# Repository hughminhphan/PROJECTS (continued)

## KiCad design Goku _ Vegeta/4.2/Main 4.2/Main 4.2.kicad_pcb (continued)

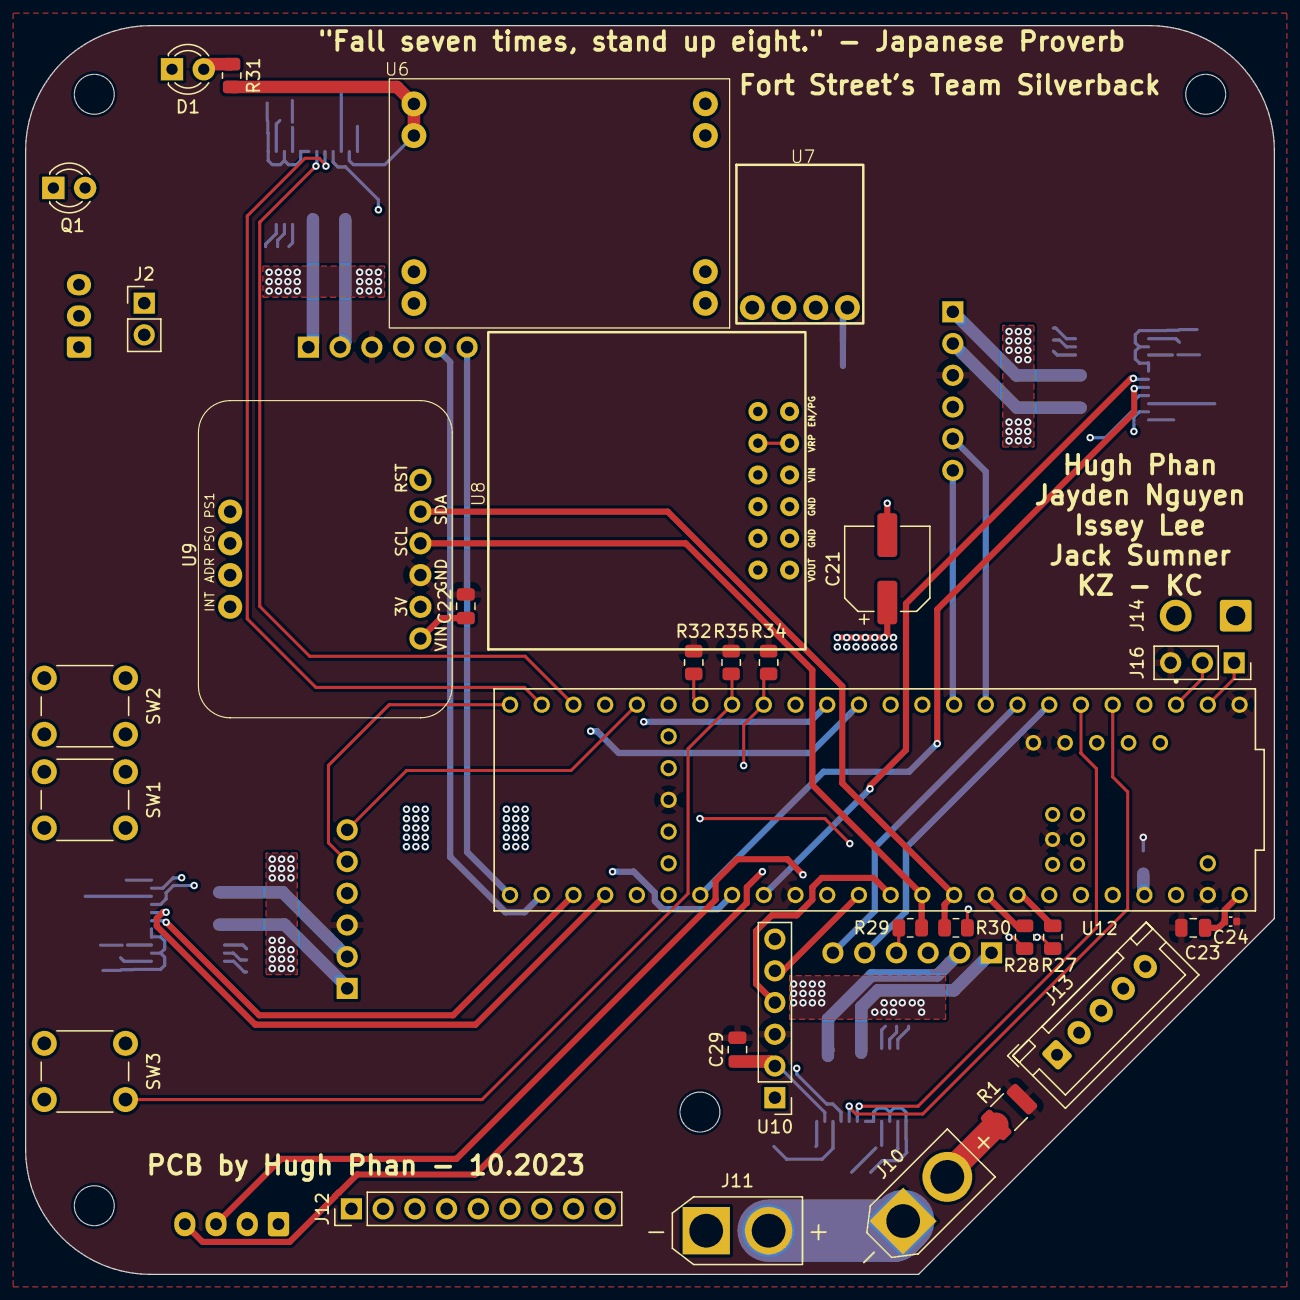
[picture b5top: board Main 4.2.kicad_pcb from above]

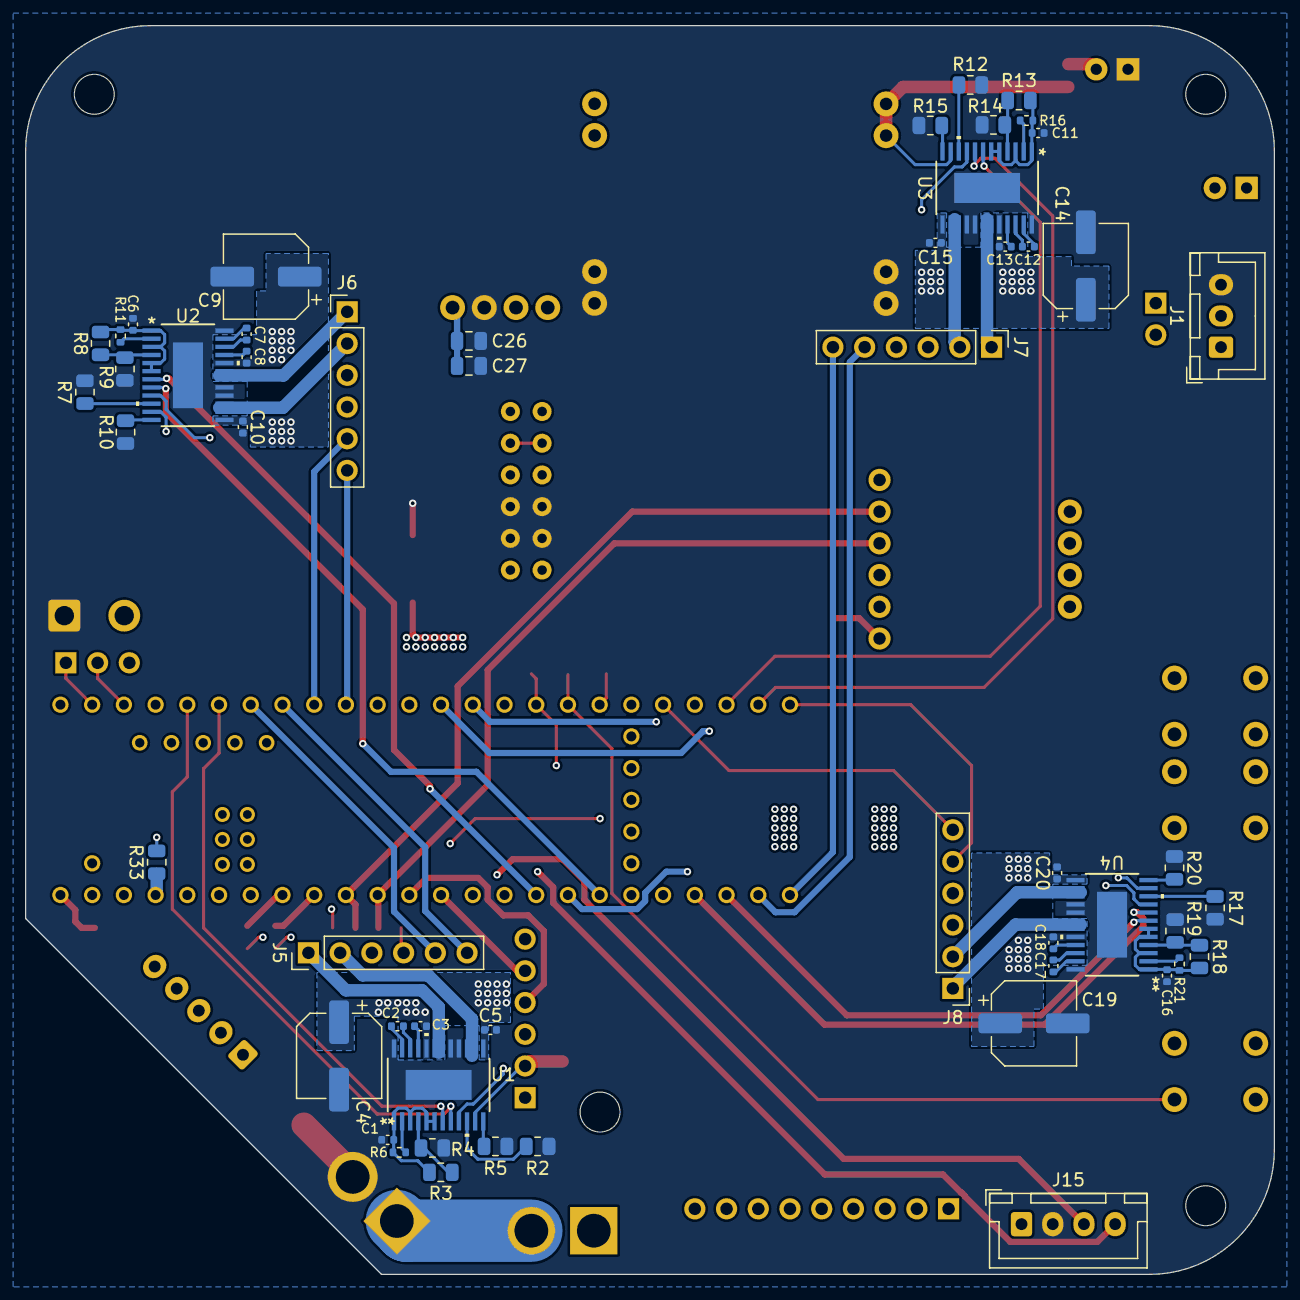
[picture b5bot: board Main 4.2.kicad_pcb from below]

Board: 4 copper layers, 100.0 x 100.0 mm, 89 parts (53 on the bottom side), 85 nets.

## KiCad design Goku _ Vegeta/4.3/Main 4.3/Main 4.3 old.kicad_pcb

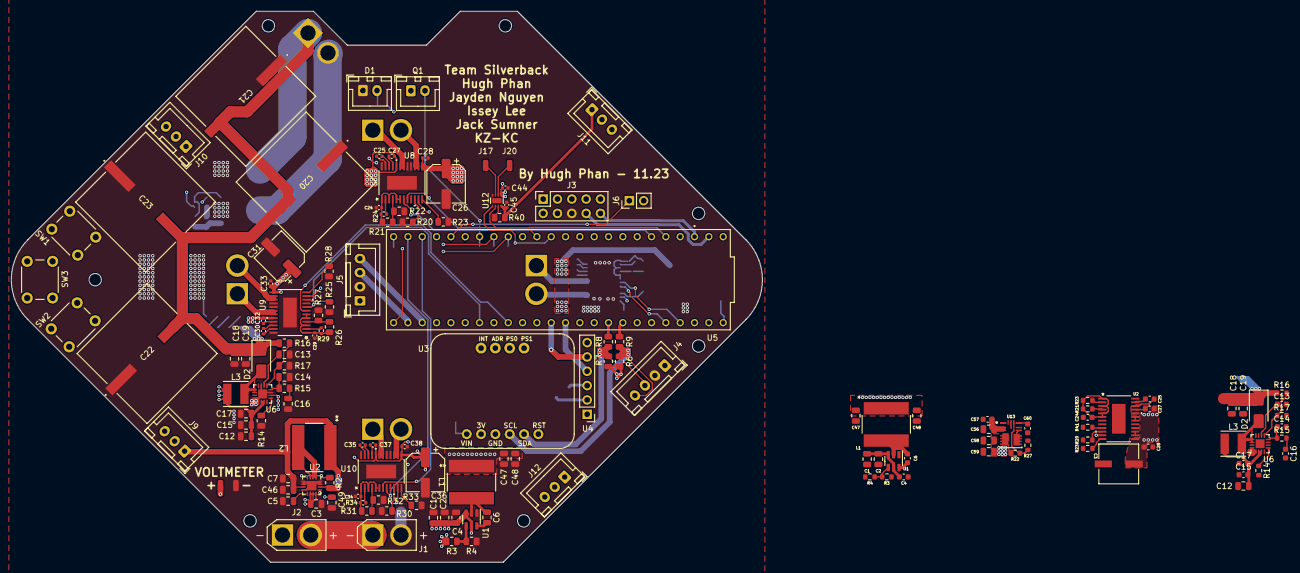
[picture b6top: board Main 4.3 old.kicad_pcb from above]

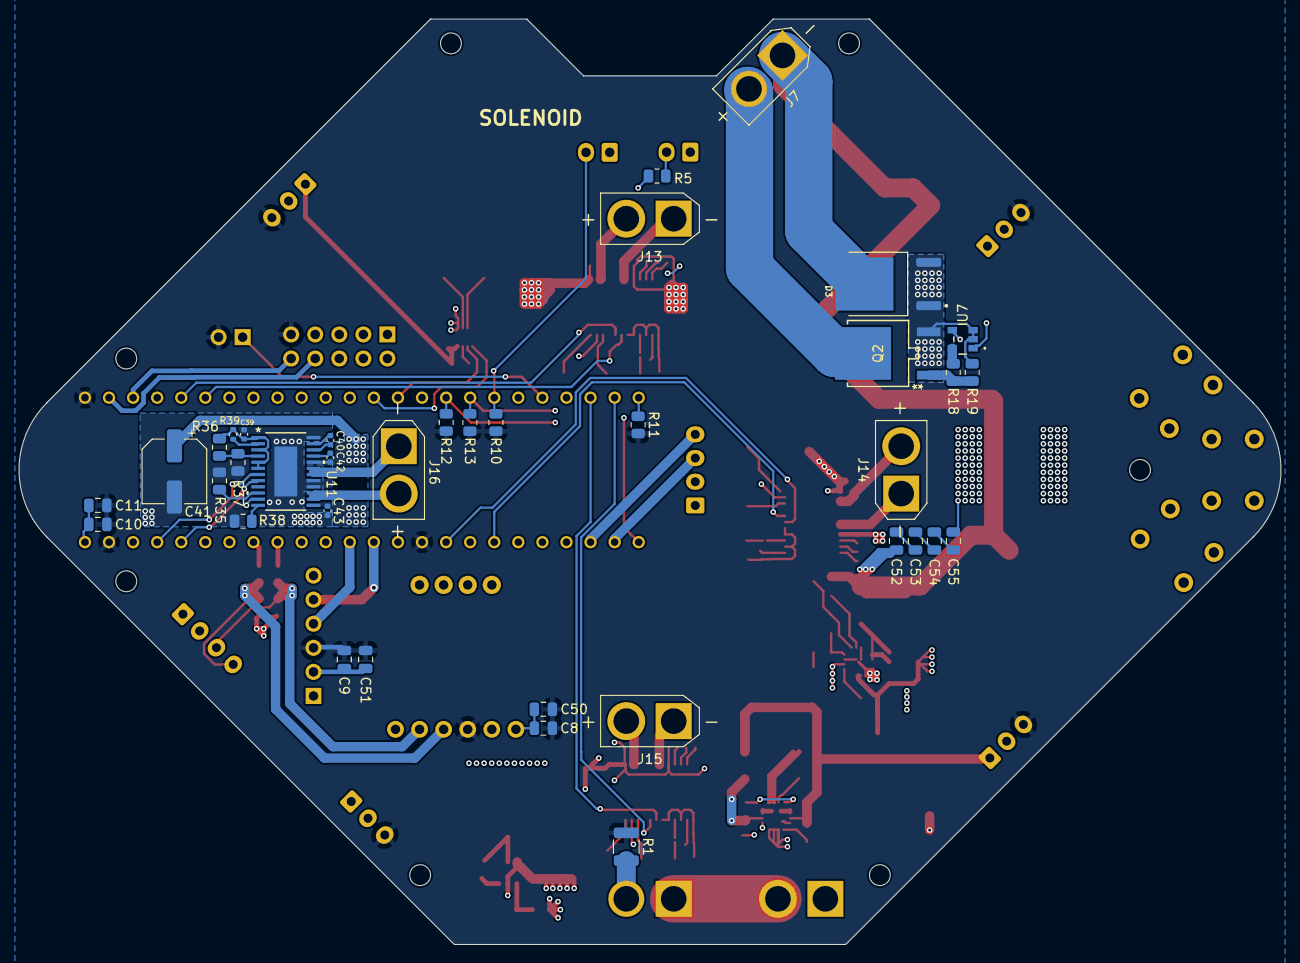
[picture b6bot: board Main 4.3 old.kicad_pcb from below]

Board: 4 copper layers, 133.1 x 97.6 mm, 188 parts (37 on the bottom side), 99 nets.

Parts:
C1, C1#2, C2, C2#2, C3#2, C7, C8, C9, C11, C47#2, C48#2: 10uF; C_0805_2012Metric
C3: 865080445010; CAP_WCAP-ASLI_06p3X07p7_WRE
C4, C17: 100nF; C_0603_1608Metric
C4#2, C17#2, C19, C19#2, C46, C49, C50, C51: 100nF; C_0805_2012Metric
C5: 470pF; C_0805_2012Metric
C6, C28, C57: 0.1uF; C_0603_1608Metric
C6#2, C10: 0.1uF; C_0805_2012Metric
C12, C12#2, C56: 4.7uF; C_0805_2012Metric
C13: 10nF; C_0805_2012Metric
C13#2: 10nF; C_0603_1608Metric
C14: 270pF; C_0805_2012Metric
C14#2: 270pF; C_0603_1608Metric
C15: 1uF; C_0805_2012Metric
C15#2, C24, C27#2, C60: 1uF; C_0603_1608Metric
C16: 56nF; C_0805_2012Metric
C16#2: 56nF; C_0603_1608Metric
C18, C18#2, C47, C48, C58, C59: 22uF; C_0805_2012Metric
C20, C21, C22, C23: 865060663015; CAP_WCAP-ASLL_16p0X17p0_WRE
C24#2, C27, C29, C32, C34, C37, C39, C42: 1uF; C_0402_1005Metric
C25: 47nF; C_0603_1608Metric
C25#2, C30, C35, C40: 47nF; C_0402_1005Metric
C26, C31, C36, C41: 100uF; CP_Elec_6.3x7.7
C28#2, C33, C38, C43, C44, C45: 0.1uF; C_0402_1005Metric
C52, C53, C54, C55: 470nF; C_0805_2012Metric
D1: LED; JST_XH_B2B-XH-A_1x02_P2.50mm_Vertical
D2, D2#2: D_Schottky; D_SMA
D3: SBRD10200TR; DPAK228P1005X240-4N
H1, H2, H3, H4, H5, H6, H7: MountingHole; MountingHole_2.2mm_M2
J1: 4S Battery; AMASS_XT30U-M_1x02_P5.0mm_Vertical
J2: Power Switch; AMASS_XT30U-F_1x02_P5.0mm_Vertical
J3: Conn_02x05_Odd_Even; PinSocket_2x05_P2.54mm_Vertical
J4: Conn_01x04; JST_XH_B4B-XH-A_1x04_P2.50mm_Vertical
J5: OpenMV; JST_XH_B4B-XH-A_1x04_P2.50mm_Vertical
J6: Superteam Reciever; PinHeader_1x02_P2.54mm_Vertical
J7: Solenoid; AMASS_XT30U-M_1x02_P5.0mm_Vertical
J9: Encoder 1; JST_XH_B3B-XH-A_1x03_P2.50mm_Vertical
J10: Encoder 2; JST_XH_B3B-XH-A_1x03_P2.50mm_Vertical
J11: Encoder 3; JST_XH_B3B-XH-A_1x03_P2.50mm_Vertical
J12: Encoder 4; JST_XH_B3B-XH-A_1x03_P2.50mm_Vertical
J13: Motor 1; AMASS_XT30U-F_1x02_P5.0mm_Vertical
J14: Motor 2; AMASS_XT30U-F_1x02_P5.0mm_Vertical
J15: Motor 3; AMASS_XT30U-F_1x02_P5.0mm_Vertical
J16: Motor 4; AMASS_XT30U-F_1x02_P5.0mm_Vertical
J17: -Motor 5; SolderWirePad_1x01_SMD_1x2mm
J18: +VOLTMETER; SolderWirePad_1x01_SMD_1x2mm
J19: -VOLTMETER; SolderWirePad_1x01_SMD_1x2mm
J20: +Motor 5; SolderWirePad_1x01_SMD_1x2mm
L1, L1#2, L2: SRN8040-2R2Y; IND_BOURNS_SRN8040
L3, L3#2: SRN4018-330M; IND_BOURNS_SRN4018
Q1: Q_Photo_NPN; JST_XH_B2B-XH-A_1x02_P2.50mm_Vertical
Q2: DMN10H170SK3-13; QNMOS1G2D3S_TO252DPAK_DIO
R1: 0R; R_1210_3225Metric
R2: 100K; R_0805_2012Metric
R3: 54K9; R_0603_1608Metric
R3#2, R4#2, R20#2, R23, R25, R28, R30, R33, R35, R38: 363R; R_0805_2012Metric
R4, R14#2: 10K; R_0603_1608Metric
R5: 95R; R_0805_2012Metric
R6, R7: 4K7; R_0805_2012Metric
R8, R9, R18: 10R; R_0805_2012Metric
R10, R11, R12, R13, R14, R19: 10K; R_0805_2012Metric
R15: 931R; R_0603_1608Metric
R15#2: 931R; R_0805_2012Metric
R16: 118K; R_0603_1608Metric
R16#2: 118K; R_0805_2012Metric
R17: 2K49; R_0805_2012Metric
R17#2: 2K49; R_0603_1608Metric
R20, R23#2: 363R; R_0603_1608Metric
R21: 0R; R_0603_1608Metric
R21#2, R26, R31, R36: 0R; R_0805_2012Metric
R22, R23#3, R27#2: 10k; R_0603_1608Metric
R22#2, R27, R32, R37: 3M; R_0805_2012Metric
R24, R29, R34, R39: 10k; R_0402_1005Metric
R40: 100R; R_0805_2012Metric
R41: 1K; R_0603_1608Metric
SW1, SW2, SW3: SPST; SW_PUSH_6mm_H4.3mm
U1, U1#2: TPS565208; SOT-23-6
U2, U8, U9, U10, U11: DRV8873HPWPR; PWP24_TEX
U2#2: TPS62142; VQFN-16-1EP_3x3mm_P0.5mm_EP1.68x1.68mm
U3: Adafruit_BNO055_STEMMA_QT; Adafruit IMU BNO055
U4: Bluetooth_Module_(HC-05); PinHeader_1x06_P2.54mm_Vertical
U5: DEV-16771; MODULE_DEV-16771
U6, U6#2: LM51581RTER; WQFN-16-1EP_3x3mm_P0.5mm_EP1.6x1.6mm
U7: DGD0211CWT-7; TSOT25-TH_DIO
U12: DRV8837; WSON-8-1EP_2x2mm_P0.5mm_EP0.9x1.6mm
U13: TPSM33625RDNR; QFN-FCMOD11_RDN_TEX

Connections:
+3V3: C7.1, C8.1, C45.1, C46.1, C50.1, C58.1, C59.1, J9.1, J10.1, J11.1, J12.1, L2.1, Q1.1 (C), R2.2, R6.1, R7.1, R22.2, R40.1, SW1.1 (A), SW2.1 (A), SW3.1 (A), U2#2.7 (FSW), U2#2.14 (VOS), U3.1 (VIN), U12.8 (VCC), U13.4 (VOUT)
+5V: C9.1, C10.1, C11.1, C47.1, C47#2.1, C48.1, C48#2.1, C51.1, J3.2, J3.4, J5.1, L1.1, L1#2.1, R3.1, R3#2.1, R5.1, U2.11 (NSLEEP), U4.2 (VCC), U5.VIN, U8.11 (NSLEEP), U9.11 (NSLEEP), U10.11 (NSLEEP), U11.11 (NSLEEP)
+15V: C1.1, C1#2.1, C2.1, C2#2.1, C3.1, C3#2.1, C4.1, C4#2.1, C12.1, C12#2.1, C15.2, C15#2.2, C17.2, C17#2.2, C26.1, C27.2, C27#2.2, C28.1, C28#2.1, C31.1, C32.2, C33.1, C36.1, C37.2, C38.1, C41.1, C42.2, C43.1, C44.1, C49.1, C56.1, C57.1, J2.1, J4.1, J18.1, L3.2, L3#2.2, U1.3 (VIN), U1.5 (EN), U1#2.3 (VIN), U1#2.5 (EN), U2.13 (VM), U2.20 (VM), U2#2.10 (AVIN), U2#2.11 (PVIN), U2#2.12 (PVIN), U2#2.13 (EN), U6.2 (VCC), U6.3 (BIAS), U6.6 (EN_UVLO_SYNC), U6#2.2 (VCC), U6#2.3 (BIAS), U6#2.6 (EN_UVLO_SYNC), U7.1 (VCC), U8.13 (VM), U8.20 (VM), U9.13 (VM), U9.20 (VM), U10.13 (VM), U10.20 (VM), U11.13 (VM), U11.20 (VM), U12.1 (VM), U13.2 (EN), U13.3 (VIN)
+48V: C18.1, C18#2.1, C19.1, C19#2.1, C20.2, C21.2, C22.2, C23.2, C52.1, D2.1 (K), D2#2.1 (K), D3.2, J7.1, R16.1, R16#2.1
/BEAMBRK: Q1.2 (E), R10.1, U5.26 (A12)
/ENC1: J9.2, U5.27 (A13)
/ENC2: J10.2, U5.16 (A2)
/ENC3: J11.2, U5.20 (A6)
/ENC4: J12.2, U5.17 (A3)
/KICK: U5.33 (MCLK2), U7.4 (*IN)
/M1A: J13.1, U2.18 (OUT1), U2.19 (OUT1), U8.18 (OUT1), U8.19 (OUT1)
/M1B: J13.2, U2.14 (OUT2), U2.15 (OUT2), U8.14 (OUT2), U8.15 (OUT2)
/M1IN1: U2.7 (EN/IN1), U5.4 (BCLK2), U8.7 (EN/IN1)
/M1IN2: U2.8 (PH/IN2), U5.3 (LRCLK2), U8.8 (PH/IN2)
/M2A: J14.1, U9.18 (OUT1), U9.19 (OUT1)
/M2B: J14.2, U9.14 (OUT2), U9.15 (OUT2)
/M2IN1: U5.41 (A17), U9.7 (EN/IN1)
/M2IN2: U5.39 (A15), U9.8 (PH/IN2)
/M3A: J15.1, U10.18 (OUT1), U10.19 (OUT1)
/M3B: J15.2, U10.14 (OUT2), U10.15 (OUT2)
/M3IN1: U5.30 (CRX3), U10.7 (EN/IN1)
/M3IN2: U5.31 (CTX3), U10.8 (PH/IN2)
/M4A: J16.1, U11.18 (OUT1), U11.19 (OUT1)
/M4B: J16.2, U11.14 (OUT2), U11.15 (OUT2)
/M4IN1: U5.23 (A9), U11.7 (EN/IN1)
/M4IN2: U5.22 (A8), U11.8 (PH/IN2)
/M5A: J20.1, U12.2 (OUT1)
/M5B: J17.1, U12.3 (OUT2)
/M5IN1: U5.12 (MISO), U12.6 (IN1)
/M5IN2: U5.11 (MOSI), U12.5 (IN2)
/MVRX: J5.4, U5.35 (TX8)
/MVTX: J5.3, U5.34 (RX8)
/RPIRX: J3.10, U5.1 (TX1)
/RPITX: J3.8, U5.0 (RX1)
/RX3: U4.4 (TX), U5.15 (A1)
/SCL: J4.4, R6.2, R9.1, U3.4 (SCL)
/SDA: J4.3, R7.2, R8.1, U3.5 (SDA)
/SUPERTMTX: J6.1, U5.28 (RX7)
/SW1: R11.1, SW1.2 (B), U5.32 (OUT1B)
/SW2: R12.1, SW2.2 (B), U5.24 (A10)
/SW3: R13.1, SW3.2 (B), U5.25 (A11)
/TX3: U4.5 (RX), U5.14 (A0)
GNDPWR: C1.2, C1#2.2, C2.2, C2#2.2, C3.2, C3#2.2, C4.2, C4#2.2, C5.2, C7.2, C12.2, C12#2.2, C13.2, C13#2.2, C14.2, C14#2.2, C15.1, C15#2.1, C16.2, C16#2.2, C17.1, C17#2.1, C18.2, C18#2.2, C19.2, C19#2.2, C20.1, C21.1, C22.1, C23.1, C24.2, C24#2.2, C26.2, C28.2, C28#2.2, C29.2, C31.2, C33.2, C34.2, C36.2, C38.2, C39.2, C41.2, C43.2, C44.2, C45.2, C46.2, C47.2, C47#2.2, C48.2, C48#2.2, C49.2, C55.2, D1.1 (K), D3.1, D3.3, J1.2, J3.6, J4.2, J5.2, J19.1, Q2.3 (S), R1.2, R4.2, R4#2.2, R14.2, R14#2.2, R17.2, R17#2.2, R19.2, R20.2, R20#2.2, R22#2.2, R23.2, R23#2.2, R25.2, R27.2, R28.2, R30.2, R32.2, R33.2, R35.2, R37.2, R38.2, R41.2, U1.1 (GND), U1#2.1 (GND), U2.16 (SRC), U2.17 (SRC), U2.24 (GND), U2#2.5 (FB), U2#2.6 (AGND), U2#2.8 (DEF), U2#2.15 (PGND), U2#2.16 (PGND), U2#2.17 (EP), U6.1 (PGND), U6.7 (AGND), U6.11 (MODE), U6.16 (PGND), U6#2.1 (PGND), U6#2.7 (AGND), U6#2.11 (MODE), U6#2.16 (PGND), U6#2.17 (EP), U7.2 (COM), U7.3 (IN), U8.16 (SRC), U8.17 (SRC), U8.24 (GND), U8.EPAD, U9.16 (SRC), U9.17 (SRC), U9.24 (GND), U9.EPAD, U10.16 (SRC), U10.17 (SRC), U10.24 (GND), U10.EPAD, U11.16 (SRC), U11.17 (SRC), U11.24 (GND), U11.EPAD, U12.4 (GND), U12.9 (GND)
GNDS: C8.2, C9.2, C10.2, C11.2, C50.2, C51.2, J3.9, J6.2, J9.3, J10.3, J11.3, J12.3, R1.1, R10.2, R11.2, R12.2, R13.2, U3.3 (GND), U4.3 (GND), U5.GND1 (GND), U5.GND2 (GND__1), U5.GND3 (GND__2)
unnamed: C16.1, C16#2.1, R15.2, R15#2.2
unnamed: C52.2, C53.1
unnamed: C53.2, C54.1
unnamed: C54.2, C55.1
unnamed: D1.2 (A), R5.2
unnamed: D2.2 (A), D2#2.2 (A), L3.1, L3#2.1, U6.13 (SW), U6.14 (SW), U6#2.13 (SW), U6#2.14 (SW)
unnamed: J1.1, J2.2
unnamed: J7.2, Q2.2 (D)
unnamed: L2.2, U2#2.1 (SW), U2#2.2 (SW), U2#2.3 (SW)
unnamed: Q2.1 (G), R18.2, R19.1
unnamed: C6.1, C6#2.1, L1.2, L1#2.2, U1.2 (SW), U1#2.2 (SW)
unnamed: C6.2, C6#2.2, U1.6 (VBST), U1#2.6 (VBST)
unnamed: R3.2, R3#2.2, R4.1, R4#2.1, U1.4 (VFB), U1#2.4 (VFB)
unnamed: R2.1, U2#2.4 (PG)
unnamed: C5.1, U2#2.9 (SS/TR)
unnamed: R8.2, U5.18 (A4)
unnamed: R9.2, U5.19 (A5)
unnamed: C14.1, C14#2.1, R15.1, R15#2.1, U6.8 (COMP), U6#2.8 (COMP)
unnamed: R16.2, R16#2.2, R17.1, R17#2.1, U6.9 (FB), U6#2.9 (FB)
unnamed: R14.1, R14#2.1, U6.5 (RT), U6#2.5 (RT)
unnamed: C13.1, C13#2.1, U6.10 (SS), U6#2.10 (SS)
unnamed: R18.1, U7.5 (OUT)
unnamed: C25.2, C25#2.2, U2.22 (CPH), U8.22 (CPH)
unnamed: C25.1, C25#2.1, U2.23 (CPL), U8.23 (CPL)
unnamed: C24.1, C24#2.1, R21.1, R21#2.1, R23#3.1, R24.1, U2.1 (DVDD), U2.3 (MODE), U2.5 (NITRIP), U2.6 (NOL), U8.1 (DVDD), U8.3 (MODE), U8.5 (NITRIP), U8.6 (NOL)
unnamed: R20.1, R20#2.1, U2.10 (IPROPI1), U8.10 (IPROPI1)
unnamed: R23.1, R23#2.1, U2.12 (IPROPI2), U8.12 (IPROPI2)
unnamed: R23#3.2, R24.2, U2.2 (NFAULT), U8.2 (NFAULT)
unnamed: R21.2, R21#2.2, R22#2.1, U2.4 (SR), U8.4 (SR)
unnamed: C27.1, C27#2.1, U2.21 (VCP), U8.21 (VCP)
unnamed: C30.2, U9.22 (CPH)
unnamed: C30.1, U9.23 (CPL)
unnamed: C29.1, R26.1, R29.1, U9.1 (DVDD), U9.3 (MODE), U9.5 (NITRIP), U9.6 (NOL)
unnamed: R25.1, U9.10 (IPROPI1)
unnamed: R28.1, U9.12 (IPROPI2)
unnamed: R29.2, U9.2 (NFAULT)
unnamed: R26.2, R27.1, U9.4 (SR)
unnamed: C32.1, U9.21 (VCP)
unnamed: C35.2, U10.22 (CPH)
unnamed: C35.1, U10.23 (CPL)
unnamed: C34.1, R31.1, R34.1, U10.1 (DVDD), U10.3 (MODE), U10.5 (NITRIP), U10.6 (NOL)
unnamed: R30.1, U10.10 (IPROPI1)
unnamed: R33.1, U10.12 (IPROPI2)
unnamed: R34.2, U10.2 (NFAULT)
unnamed: R31.2, R32.1, U10.4 (SR)
unnamed: C37.1, U10.21 (VCP)
unnamed: C40.2, U11.22 (CPH)
unnamed: C40.1, U11.23 (CPL)
unnamed: C39.1, R36.1, R39.1, U11.1 (DVDD), U11.3 (MODE), U11.5 (NITRIP), U11.6 (NOL)
unnamed: R35.1, U11.10 (IPROPI1)
unnamed: R38.1, U11.12 (IPROPI2)
unnamed: R39.2, U11.2 (NFAULT)
unnamed: R36.2, R37.1, U11.4 (SR)
unnamed: C42.1, U11.21 (VCP)
unnamed: R40.2, U12.7 (~SLEEP)
